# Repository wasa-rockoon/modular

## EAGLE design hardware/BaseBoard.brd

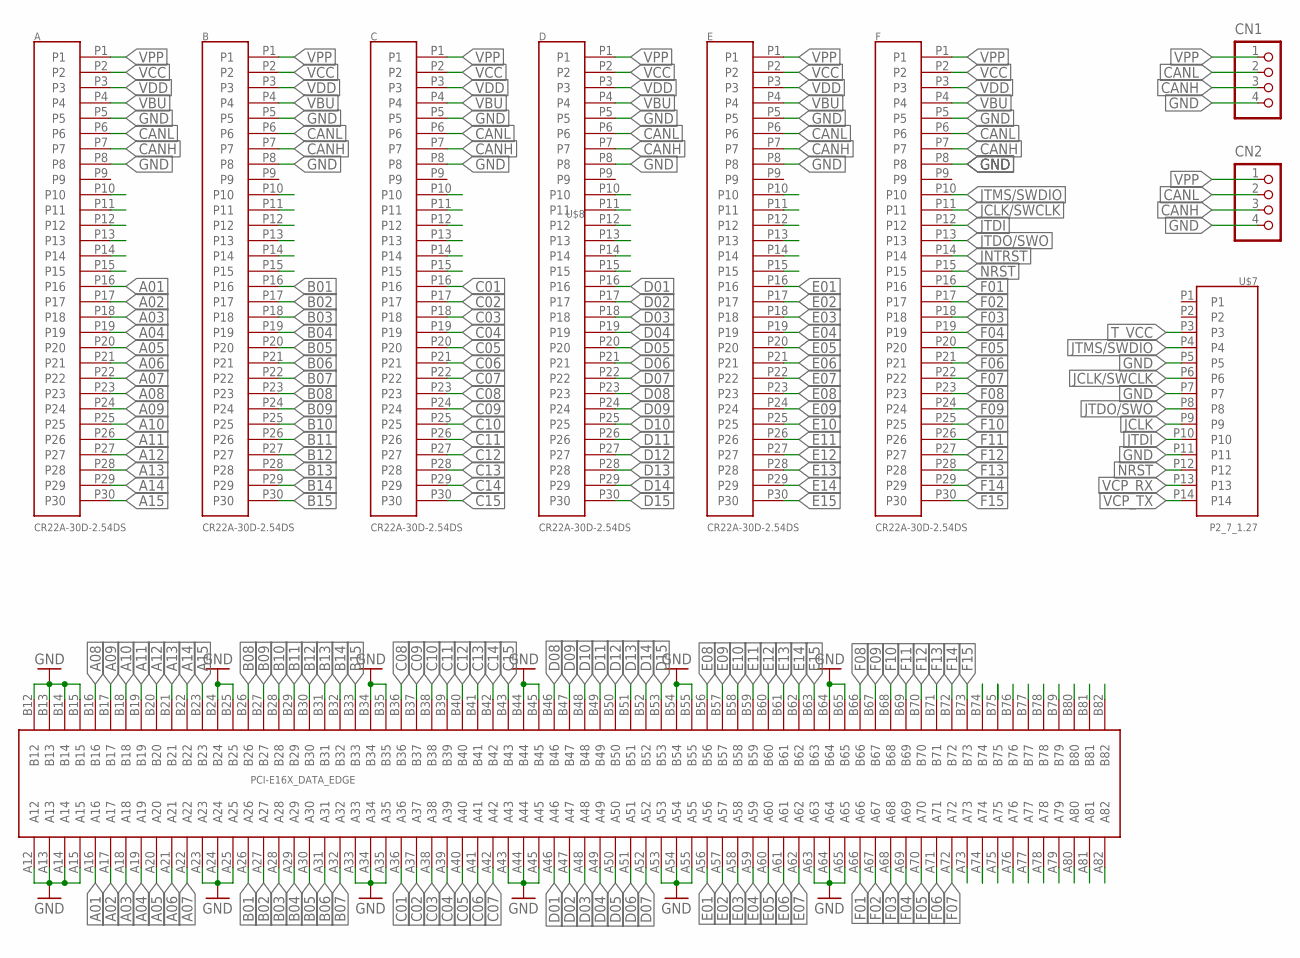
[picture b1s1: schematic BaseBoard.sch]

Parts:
A: CR22A-30D-2.54DS
B: CR22A-30D-2.54DS
C: CR22A-30D-2.54DS
CN1, CN2: B4B-PH-K-S
D: CR22A-30D-2.54DS
E: CR22A-30D-2.54DS
F: CR22A-30D-2.54DS
U$7: P2_7_1.27
U$8: PCI-E16X_DATA_EDGE; PCI-E_164_DATA_EDGE

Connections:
!JNTRST!: F.P14
!NRST!: F.P15, U$7.P12
A01: A.P16, U$8.A16
A02: A.P17, U$8.A17
A03: A.P18, U$8.A18
A04: A.P19, U$8.A19
A05: A.P20, U$8.A20
A06: A.P21, U$8.A21
A07: A.P22, U$8.A22
A08: A.P23, U$8.B16
A09: A.P24, U$8.B17
A10: A.P25, U$8.B18
A11: A.P26, U$8.B19
A12: A.P27, U$8.B20
A13: A.P28, U$8.B21
A14: A.P29, U$8.B22
A15: A.P30, U$8.B23
B01: B.P16, U$8.A26
B02: B.P17, U$8.A27
B03: B.P18, U$8.A28
B04: B.P19, U$8.A29
B05: B.P20, U$8.A30
B06: B.P21, U$8.A31
B07: B.P22, U$8.A32
B08: B.P23, U$8.B26
B09: B.P24, U$8.B27
B10: B.P25, U$8.B28
B11: B.P26, U$8.B29
B12: B.P27, U$8.B30
B13: B.P28, U$8.B31
B14: B.P29, U$8.B32
B15: B.P30, U$8.B33
C01: C.P16, U$8.A36
C02: C.P17, U$8.A37
C03: C.P18, U$8.A38
C04: C.P19, U$8.A39
C05: C.P20, U$8.A40
C06: C.P21, U$8.A41
C07: C.P22, U$8.A42
C08: C.P23, U$8.B36
C09: C.P24, U$8.B37
C10: C.P25, U$8.B38
C11: C.P26, U$8.B39
C12: C.P27, U$8.B40
C13: C.P28, U$8.B41
C14: C.P29, U$8.B42
C15: C.P30, U$8.B43
CANH: A.P7, B.P7, C.P7, CN1.3, CN2.3, D.P7, E.P7, F.P7
CANL: A.P6, B.P6, C.P6, CN1.2, CN2.2, D.P6, E.P6, F.P6
D01: D.P16, U$8.A46
D02: D.P17, U$8.A47
D03: D.P18, U$8.A48
D04: D.P19, U$8.A49
D05: D.P20, U$8.A50
D06: D.P21, U$8.A51
D07: D.P22, U$8.A52
D08: D.P23, U$8.B46
D09: D.P24, U$8.B47
D10: D.P25, U$8.B48
D11: D.P26, U$8.B49
D12: D.P27, U$8.B50
D13: D.P28, U$8.B51
D14: D.P29, U$8.B52
D15: D.P30, U$8.B53
E01: E.P16, U$8.A56
E02: E.P17, U$8.A57
E03: E.P18, U$8.A58
E04: E.P19, U$8.A59
E05: E.P20, U$8.A60
E06: E.P21, U$8.A61
E07: E.P22, U$8.A62
E08: E.P23, U$8.B56
E09: E.P24, U$8.B57
E10: E.P25, U$8.B58
E11: E.P26, U$8.B59
E12: E.P27, U$8.B60
E13: E.P28, U$8.B61
E14: E.P29, U$8.B62
E15: E.P30, U$8.B63
F01: F.P16, U$8.A66
F02: F.P17, U$8.A67
F03: F.P18, U$8.A68
F04: F.P19, U$8.A69
F05: F.P20, U$8.A70
F06: F.P21, U$8.A71
F07: F.P22, U$8.A72
F08: F.P23, U$8.B66
F09: F.P24, U$8.B67
F10: F.P25, U$8.B68
F11: F.P26, U$8.B69
F12: F.P27, U$8.B70
F13: F.P28, U$8.B71
F14: F.P29, U$8.B72
F15: F.P30, U$8.B73
GND: A.P5, A.P8, B.P5, B.P8, C.P5, C.P8, CN1.4, CN2.4, D.P5, D.P8, E.P5, E.P8, F.P5, F.P8, U$7.P5, U$7.P7, U$7.P11, U$8.A12, U$8.A13, U$8.A14, U$8.A15, U$8.A23, U$8.A24, U$8.A25, U$8.A33, U$8.A34, U$8.A35, U$8.A43, U$8.A44, U$8.A45, U$8.A53, U$8.A54, U$8.A55, U$8.A63, U$8.A64, U$8.A65, U$8.B12, U$8.B13, U$8.B14, U$8.B15, U$8.B24, U$8.B25, U$8.B34, U$8.B35, U$8.B44, U$8.B45, U$8.B54, U$8.B55, U$8.B64, U$8.B65
JCLK: U$7.P9
JCLK/SWCLK: F.P11, U$7.P6
JTDI: F.P12, U$7.P10
JTDO/SWO: F.P13, U$7.P8
JTMS/SWDIO: F.P10, U$7.P4
T_VCC: U$7.P3
VBU: A.P4, B.P4, C.P4, D.P4, E.P4, F.P4
VCC: A.P2, B.P2, C.P2, D.P2, E.P2, F.P2
VCP_RX: U$7.P13
VCP_TX: U$7.P14
VDD: A.P3, B.P3, C.P3, D.P3, E.P3, F.P3
VPP: A.P1, B.P1, C.P1, CN1.1, CN2.1, D.P1, E.P1, F.P1

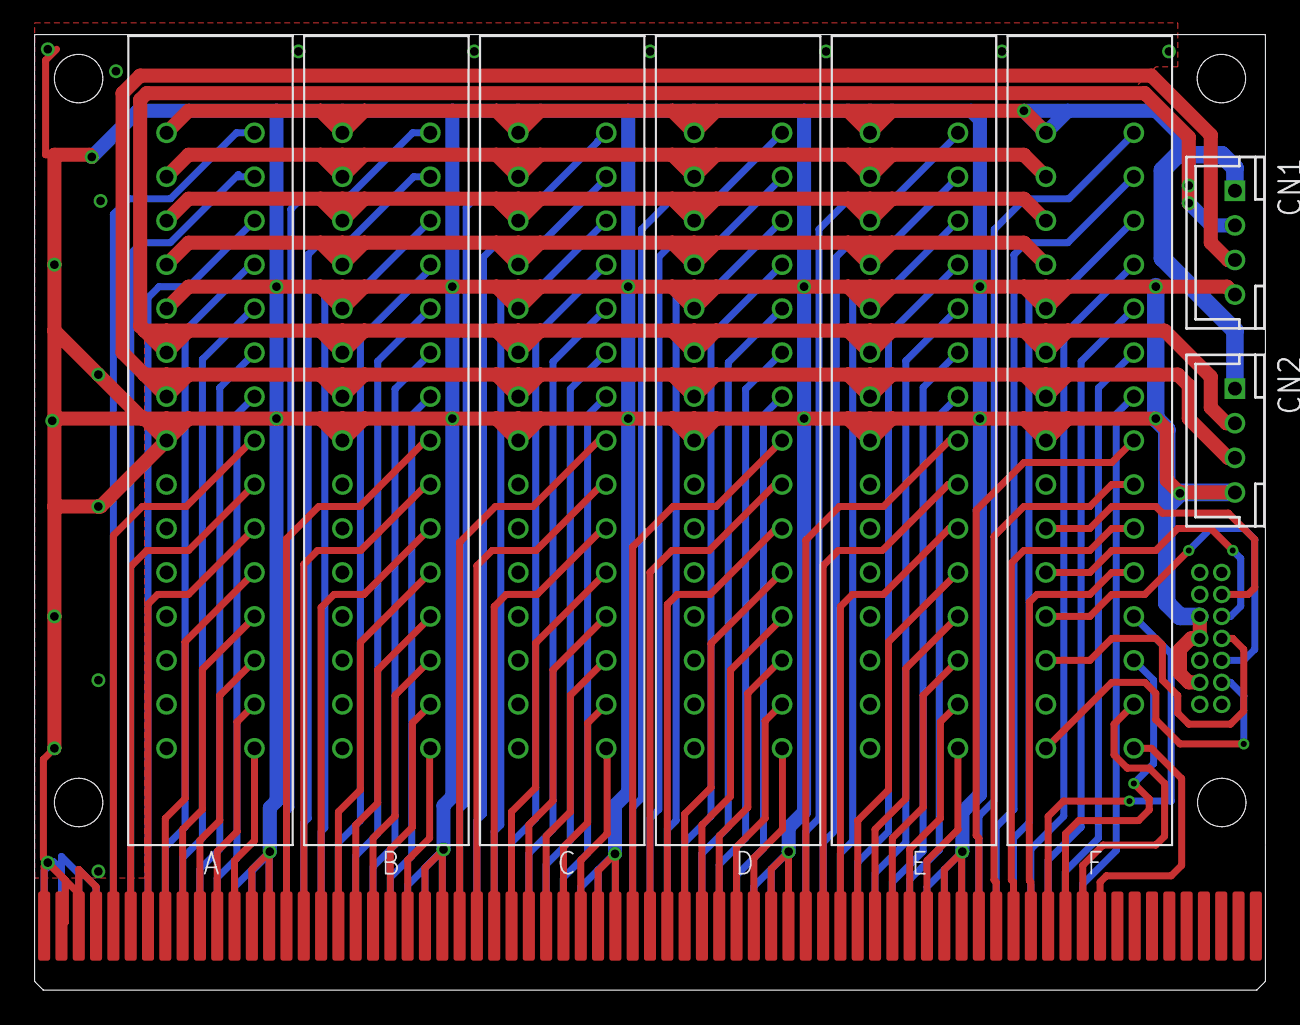
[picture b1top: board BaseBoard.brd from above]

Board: 2 copper layers, 71.1 x 55.2 mm, 10 parts (0 on the bottom side), 102 nets.

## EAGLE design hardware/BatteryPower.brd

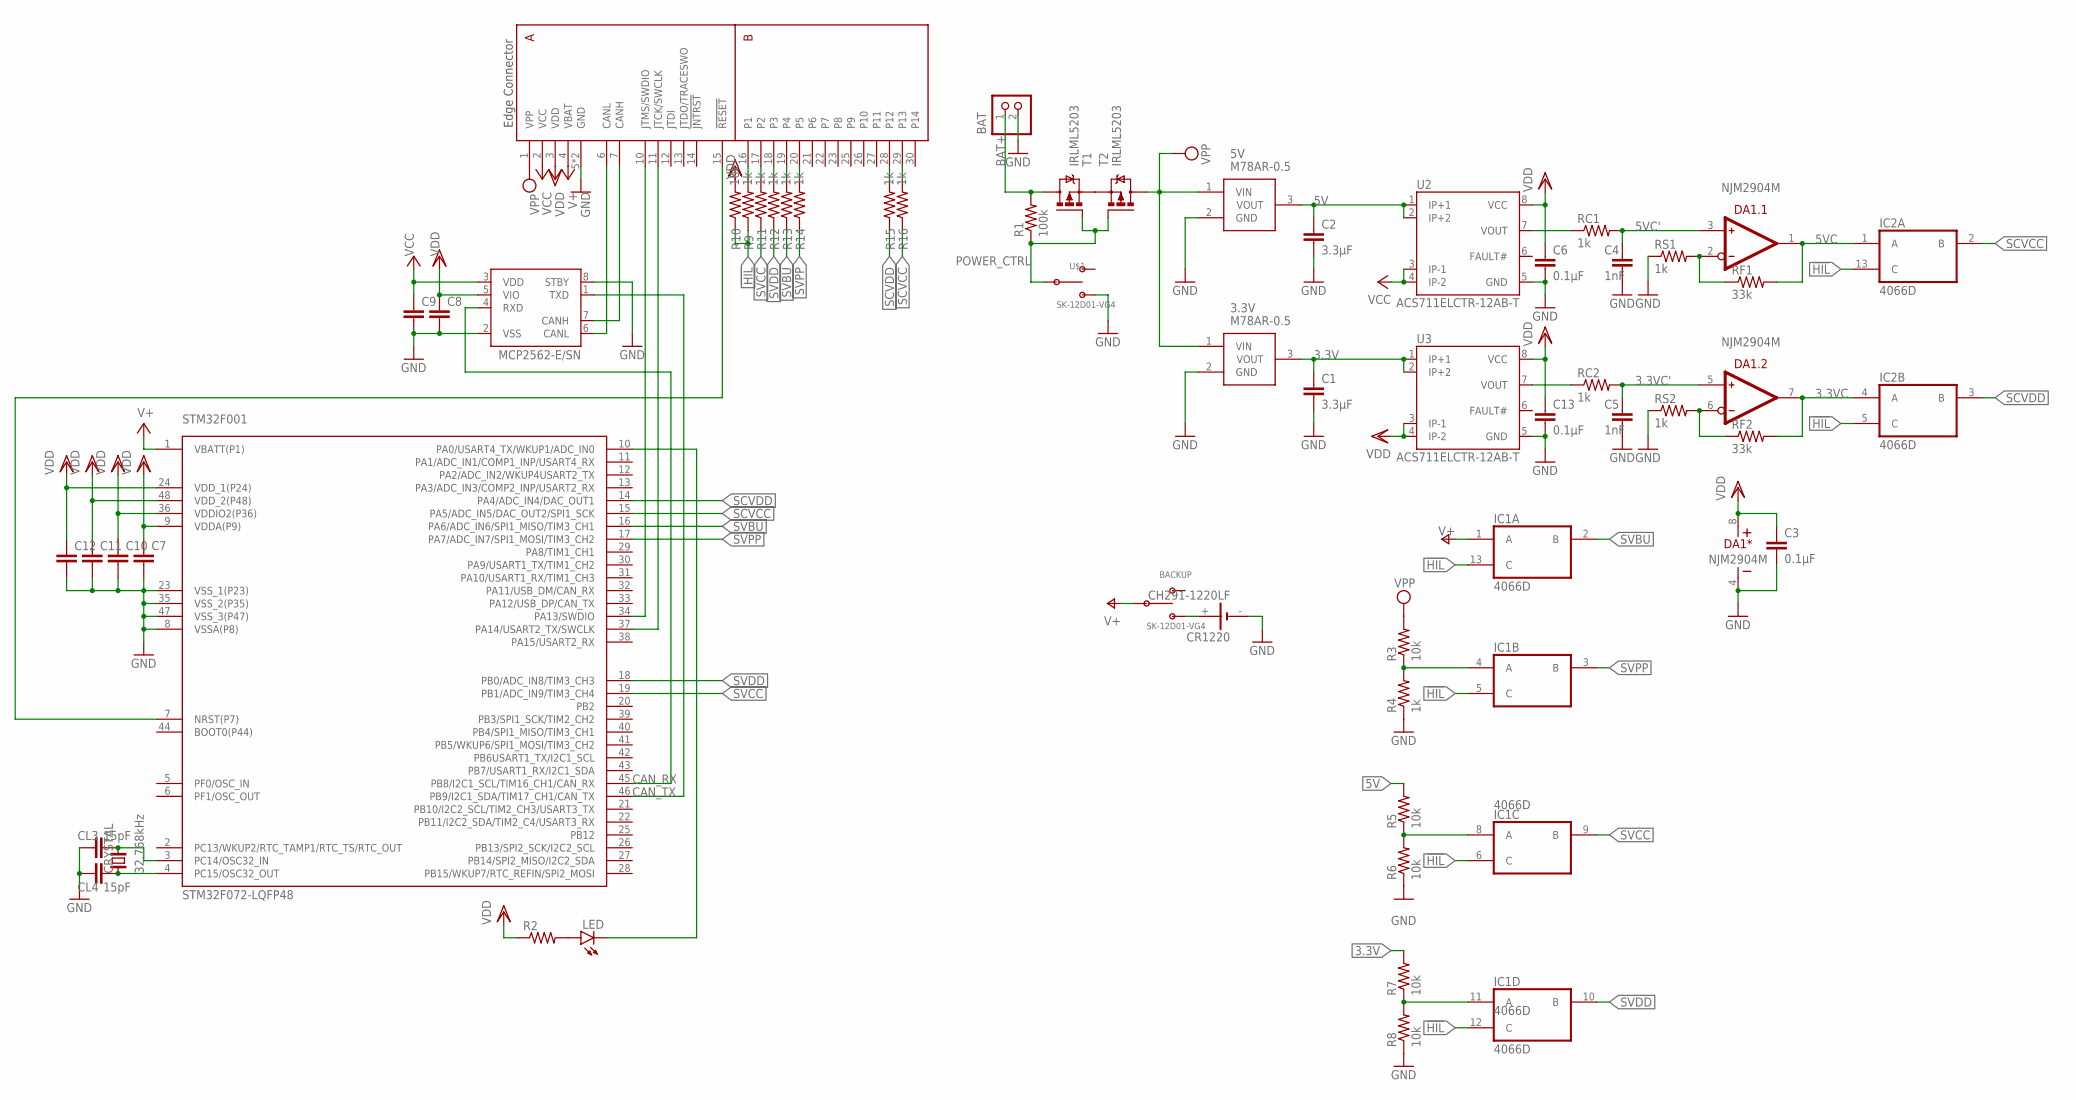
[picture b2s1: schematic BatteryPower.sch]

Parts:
3.3V, 5V: M78AR-0.5; SHDR3W75P0X254_1X3_1128X755X10
BACKUP: SK-12D01-VG4
BAT: S2B-XH-A
C1, C2: 3.3µF; C0603K
C3, C6, C13: 0.1µF; C0603K
C4, C5: 1nF; C0603K
C7, C8, C9, C10, C11, C12: C-EUC0603K; C0603K
CL3, CL4: 15pF; C0603K
CR1220: CH291-1220LF
CRYSTAL: 32.768kHz; FC-255
DA1: NJM2904M; SO-8
IC1, IC2: 4066D; SO14
LED: LEDCHIP-LED0603; CHIP-LED0603
MCP2562: MCP2562-E/SN; SOIC127P600X175-8N
R1: 100k; R0603
R2: R-US_R0603; R0603
R3, R5, R6, R7, R8, R10: 10k; R0603
R4, R9, R11, R12, R13, R14, R15, R16: 1k; R0603
RC1, RC2: 1k; R0603
RF1, RF2: 33k; R0603
RS1, RS2: 1k; R0603
STM32F001: STM32F072-LQFP48; LQFP48
T1, T2: IRLML5203; MICRO3
U2, U3: ACS711ELCTR-12AB-T; SOIC8
U$1: SK-12D01-VG4
U$2: EDGE30

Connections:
3.3V: 3.3V.3 (VOUT), C1.1, R7.2, U3.1 (IP+1), U3.2 (IP+2)
3.3VC: DA1.7 (OUT), IC2.4 (A), RF2.2
3.3VC': C5.1, DA1.5 (IN+), RC2.2
5V: 5V.3 (VOUT), C2.1, R5.2, U2.1 (IP+1), U2.2 (IP+2)
5VC: DA1.1 (OUT), IC2.1 (A), RF1.2
5VC': C4.1, DA1.3 (IN+), RC1.2
!HIL!: IC1.5 (C), IC1.6 (C), IC1.12 (C), IC1.13 (C), IC2.5 (C), IC2.13 (C), R9.1, R10.1
BAT+: BAT.1, R1.2, T1.3 (D)
BU+: BACKUP.B, CR1220.+
CANH1: MCP2562.7 (CANH), U$2.7 (CANH)
CANL1: MCP2562.6 (CANL), U$2.6 (CANL)
CAN_RX: MCP2562.4 (RXD), STM32F001.45 (PB8/I2C1_SCL/TIM16_CH1/CAN_RX)
CAN_TX: MCP2562.1 (TXD), STM32F001.46 (PB9/I2C1_SDA/TIM17_CH1/CAN_TX)
GND: 3.3V.2 (GND), 5V.2 (GND), BAT.2, C1.2, C2.2, C3.2, C4.2, C5.2, C6.2, C7.2, C8.2, C9.2, C10.2, C11.2, C12.2, C13.2, CL3.1, CL4.1, CR1220.-, DA1.4 (V-), IC1.7 (VSS), IC2.7 (VSS), MCP2562.2 (VSS), MCP2562.8 (STBY), R4.1, R6.1, R8.1, RS1.1, RS2.1, STM32F001.8 (VSSA(P8)), STM32F001.23 (VSS_1(P23)), STM32F001.35 (VSS_2(P35)), STM32F001.47 (VSS_3(P47)), U2.5 (GND), U3.5 (GND), U$1.B, U$2.5 (GND), U$2.8 (GND)
unnamed: R9.2, U$2.16 (P1)
unnamed: T1.2 (S), T2.2 (S)
unnamed: DA1.2 (IN-), RF1.1, RS1.2
unnamed: DA1.6 (IN-), RF2.1, RS2.2
unnamed: RC1.1, U2.7 (VOUT)
unnamed: RC2.1, U3.7 (VOUT)
unnamed: R16.2, U$2.29 (P13)
unnamed: R15.2, U$2.28 (P12)
unnamed: R14.2, U$2.20 (P5)
unnamed: R13.2, U$2.19 (P4)
unnamed: R12.2, U$2.18 (P3)
unnamed: CL4.2, CRYSTAL.1, STM32F001.4 (PC15/OSC32_OUT)
unnamed: CL3.2, CRYSTAL.2, STM32F001.3 (PC14/OSC32_IN)
unnamed: LED.C, STM32F001.10 (PA0/USART4_TX/WKUP1/ADC_IN0)
unnamed: R11.2, U$2.17 (P2)
unnamed: LED.A, R2.2
NRST1: STM32F001.7 (NRST(P7)), U$2.15 (!RESET!)
POWER_CTRL: R1.1, T1.1 (G), T2.1 (G), U$1.C
PVCC: IC1.8 (A), R5.1, R6.2
PVDD: IC1.11 (A), R7.1, R8.2
PVPP: IC1.4 (A), R3.1, R4.2
SCVCC: IC2.2 (B), R16.1, STM32F001.15 (PA5/ADC_IN5/DAC_OUT2/SPI1_SCK)
SCVDD: IC2.3 (B), R15.1, STM32F001.14 (PA4/ADC_IN4/DAC_OUT1)
SVBU: IC1.2 (B), R13.1, STM32F001.16 (PA6/ADC_IN6/SPI1_MISO/TIM3_CH1)
SVCC: IC1.9 (B), R11.1, STM32F001.19 (PB1/ADC_IN9/TIM3_CH4)
SVDD: IC1.10 (B), R12.1, STM32F001.18 (PB0/ADC_IN8/TIM3_CH3)
SVPP: IC1.3 (B), R14.1, STM32F001.17 (PA7/ADC_IN7/SPI1_MOSI/TIM3_CH2)
SWCLK1: STM32F001.37 (PA14/USART2_TX/SWCLK), U$2.11 (JTCK/SWCLK)
SWDIO1: STM32F001.34 (PA13/SWDIO), U$2.10 (JTMS/SWDIO)
VBAT: BACKUP.C, IC1.1 (A), STM32F001.1 (VBATT(P1)), U$2.4 (VBAT)
VCC: C9.1, MCP2562.3 (VDD), U2.3 (IP-1), U2.4 (IP-2), U$2.2 (VCC)
VDD: C3.1, C6.1, C7.1, C8.1, C10.1, C11.1, C12.1, C13.1, DA1.8 (V+), IC1.14 (VDD), IC2.14 (VDD), MCP2562.5 (VIO), R2.1, R10.2, STM32F001.9 (VDDA(P9)), STM32F001.24 (VDD_1(P24)), STM32F001.36 (VDDIO2(P36)), STM32F001.48 (VDD_2(P48)), U2.8 (VCC), U3.3 (IP-1), U3.4 (IP-2), U3.8 (VCC), U$2.3 (VDD)
VPP: 3.3V.1 (VIN), 5V.1 (VIN), R3.2, T2.3 (D), U$2.1 (VPP)

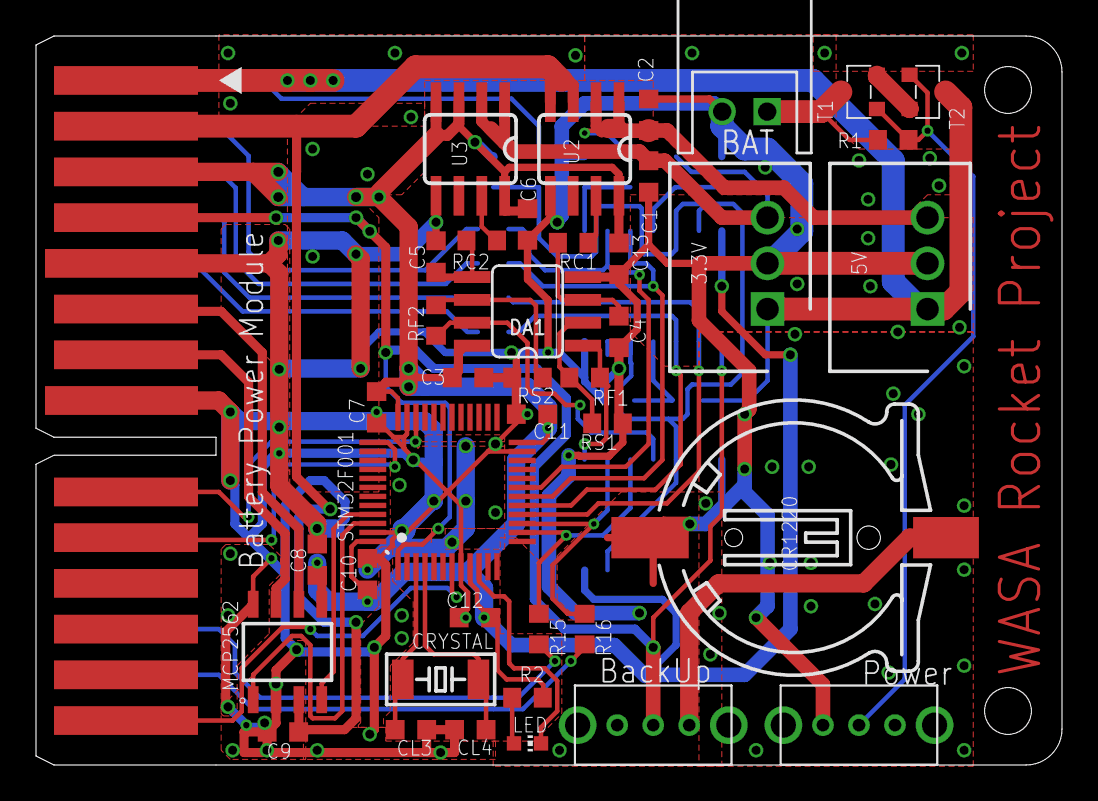
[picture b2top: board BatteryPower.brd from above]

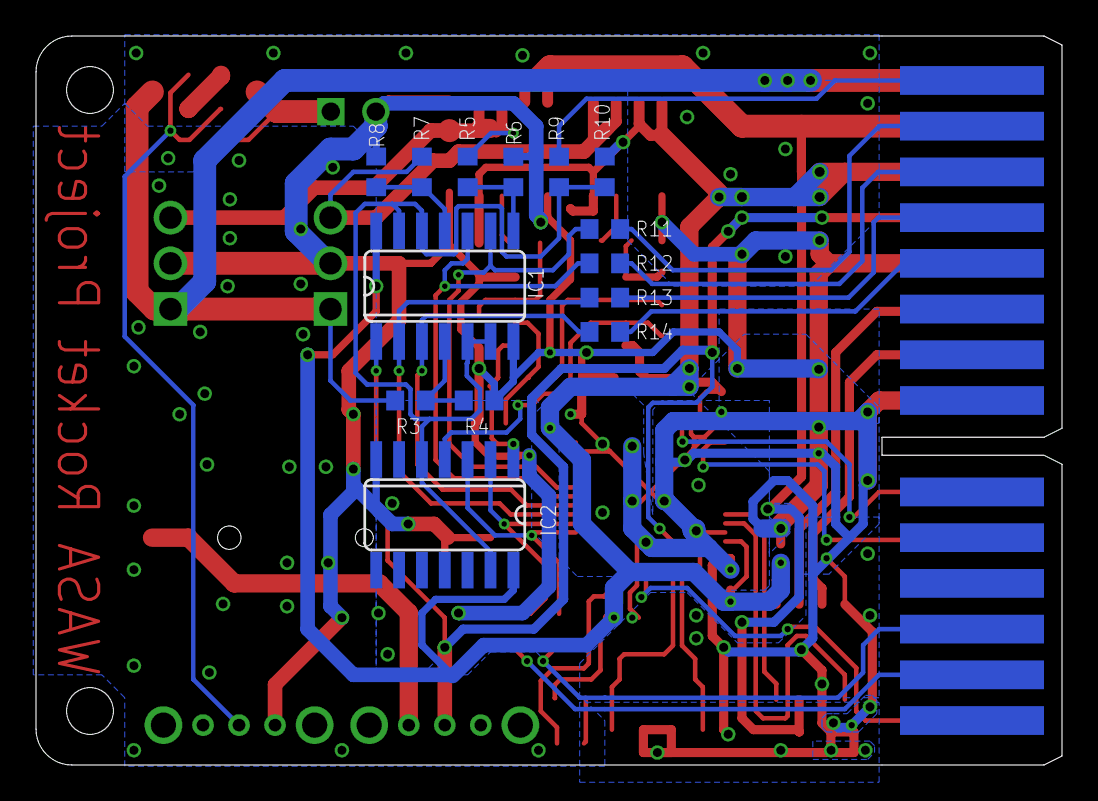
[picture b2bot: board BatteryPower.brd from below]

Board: 2 copper layers, 57.0 x 40.5 mm, 55 parts (14 on the bottom side), 47 nets.

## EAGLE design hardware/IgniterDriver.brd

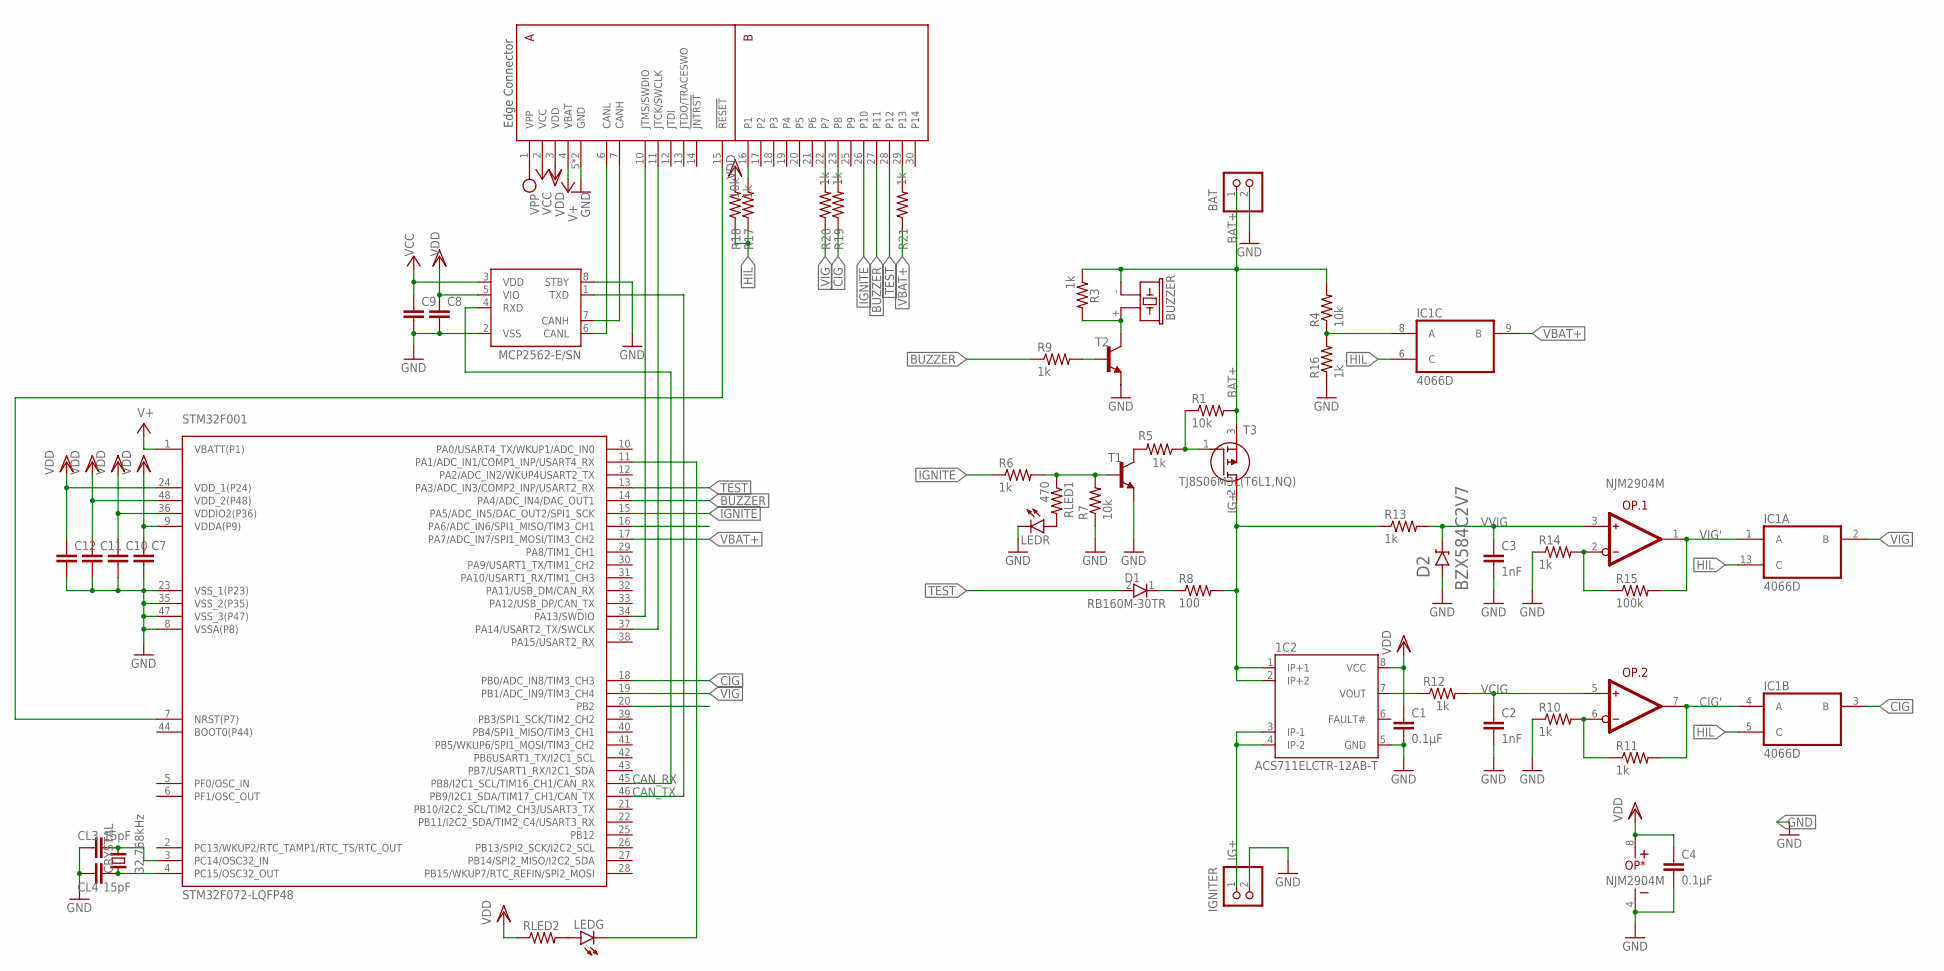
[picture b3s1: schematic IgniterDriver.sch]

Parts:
1C2: ACS711ELCTR-12AB-T; SOIC8
BAT: S2B-XH-A
BUZZER: F/CM12P
C1, C4: 0.1µF; C0603K
C2, C3: 1nF; C0603K
C7, C8, C9, C10, C11, C12: C-EUC0603K; C0603K
CL3, CL4: 15pF; C0603K
CRYSTAL: 32.768kHz; FC-255
D1: RB160M-30TR; SODFL3516X90N
D2: BZX584C2V7; BZX584C
IC1: 4066D; SO14
IGNITER: S2B-XH-A
LEDG: LEDCHIP-LED0603; CHIP-LED0603
LEDR: LEDCHIPLED_0603; CHIPLED_0603
MCP2562: MCP2562-E/SN; SOIC127P600X175-8N
OP: NJM2904M; SO-8
R1, R4, R7, R18: 10k; R0603
R3, R5, R6, R9, R10, R11, R12, R13, R14, R16, R17, R19, R20, R21: 1k; R0603
R8: 100; R0603
R15: 100k; R0603
RLED1: 470; R0603
RLED2: R-US_R0603; R0603
STM32F001: STM32F072-LQFP48; LQFP48
T1, T2: -NPN-SOT23-EBC; SOT23-EBC
T3: TJ8S06M3L(T6L1,NQ); TJ8S06M3LT6L1NQ
U$2: EDGE30

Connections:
!HIL!: IC1.5 (C), IC1.6 (C), IC1.13 (C), R17.1, R18.1
BAT+: BAT.1, BUZZER.- (2), R1.2, R3.1, R4.2, T3.3 (S)
BUZZER: R9.1, STM32F001.14 (PA4/ADC_IN4/DAC_OUT1), U$2.27 (P11)
CANH1: MCP2562.7 (CANH), U$2.7 (CANH)
CANL1: MCP2562.6 (CANL), U$2.6 (CANL)
CAN_RX: MCP2562.4 (RXD), STM32F001.45 (PB8/I2C1_SCL/TIM16_CH1/CAN_RX)
CAN_TX: MCP2562.1 (TXD), STM32F001.46 (PB9/I2C1_SDA/TIM17_CH1/CAN_TX)
CIG: IC1.3 (B), R19.1, STM32F001.18 (PB0/ADC_IN8/TIM3_CH3)
CIG': IC1.4 (A), OP.7 (OUT), R11.2
GND: 1C2.5 (GND), BAT.2, C1.2, C2.2, C3.2, C4.2, C7.2, C8.2, C9.2, C10.2, C11.2, C12.2, CL3.1, CL4.1, D2.A, IC1.7 (VSS), IGNITER.2, LEDR.C, MCP2562.2 (VSS), MCP2562.8 (STBY), OP.4 (V-), R7.1, R10.1, R14.1, R16.1, STM32F001.8 (VSSA(P8)), STM32F001.23 (VSS_1(P23)), STM32F001.35 (VSS_2(P35)), STM32F001.47 (VSS_3(P47)), T1.E, T2.E, U$2.5 (GND), U$2.8 (GND)
IG+: 1C2.3 (IP-1), 1C2.4 (IP-2), IGNITER.1
IG+': 1C2.1 (IP+1), 1C2.2 (IP+2), R8.2, R13.1, T3.2 (D)
IGNITE: R6.1, STM32F001.15 (PA5/ADC_IN5/DAC_OUT2/SPI1_SCK), U$2.26 (P10)
unnamed: R1.1, R5.1, T3.1 (G)
unnamed: R5.2, T1.C
unnamed: R6.2, R7.2, RLED1.1, T1.B
unnamed: D1.1 (K), R8.1
unnamed: BUZZER.+ (1), R3.2, T2.C
unnamed: OP.2 (IN-), R14.2, R15.1
unnamed: OP.6 (IN-), R10.2, R11.1
unnamed: LEDR.A, RLED1.2
unnamed: R9.2, T2.B
unnamed: R21.2, U$2.29 (P13)
unnamed: R19.2, U$2.23 (P8)
unnamed: R20.2, U$2.22 (P7)
unnamed: CL4.2, CRYSTAL.1, STM32F001.4 (PC15/OSC32_OUT)
unnamed: CL3.2, CRYSTAL.2, STM32F001.3 (PC14/OSC32_IN)
unnamed: LEDG.C, STM32F001.11 (PA1/ADC_IN1/COMP1_INP/USART4_RX)
unnamed: R17.2, U$2.16 (P1)
unnamed: LEDG.A, RLED2.2
NRST1: STM32F001.7 (NRST(P7)), U$2.15 (!RESET!)
SWCLK1: STM32F001.37 (PA14/USART2_TX/SWCLK), U$2.11 (JTCK/SWCLK)
SWDIO1: STM32F001.34 (PA13/SWDIO), U$2.10 (JTMS/SWDIO)
TEST: D1.2 (A), STM32F001.13 (PA3/ADC_IN3/COMP2_INP/USART2_RX), U$2.28 (P12)
VBAT+: IC1.9 (B), R21.1, STM32F001.17 (PA7/ADC_IN7/SPI1_MOSI/TIM3_CH2)
VBAT+': IC1.8 (A), R4.1, R16.2
VBU: STM32F001.1 (VBATT(P1)), U$2.4 (VBAT)
VCC: C9.1, MCP2562.3 (VDD), U$2.2 (VCC)
VCIG: C2.1, OP.5 (IN+), R12.2
VDD: 1C2.8 (VCC), C1.1, C4.1, C7.1, C8.1, C10.1, C11.1, C12.1, IC1.14 (VDD), MCP2562.5 (VIO), OP.8 (V+), R18.2, RLED2.1, STM32F001.9 (VDDA(P9)), STM32F001.24 (VDD_1(P24)), STM32F001.36 (VDDIO2(P36)), STM32F001.48 (VDD_2(P48)), U$2.3 (VDD)
VIG: IC1.2 (B), R20.1, STM32F001.19 (PB1/ADC_IN9/TIM3_CH4)
VIG': IC1.1 (A), OP.1 (OUT), R15.2
VOUT: 1C2.7 (VOUT), R12.1
VPP: U$2.1 (VPP)
VVIG: C3.1, D2.C, OP.3 (IN+), R13.2

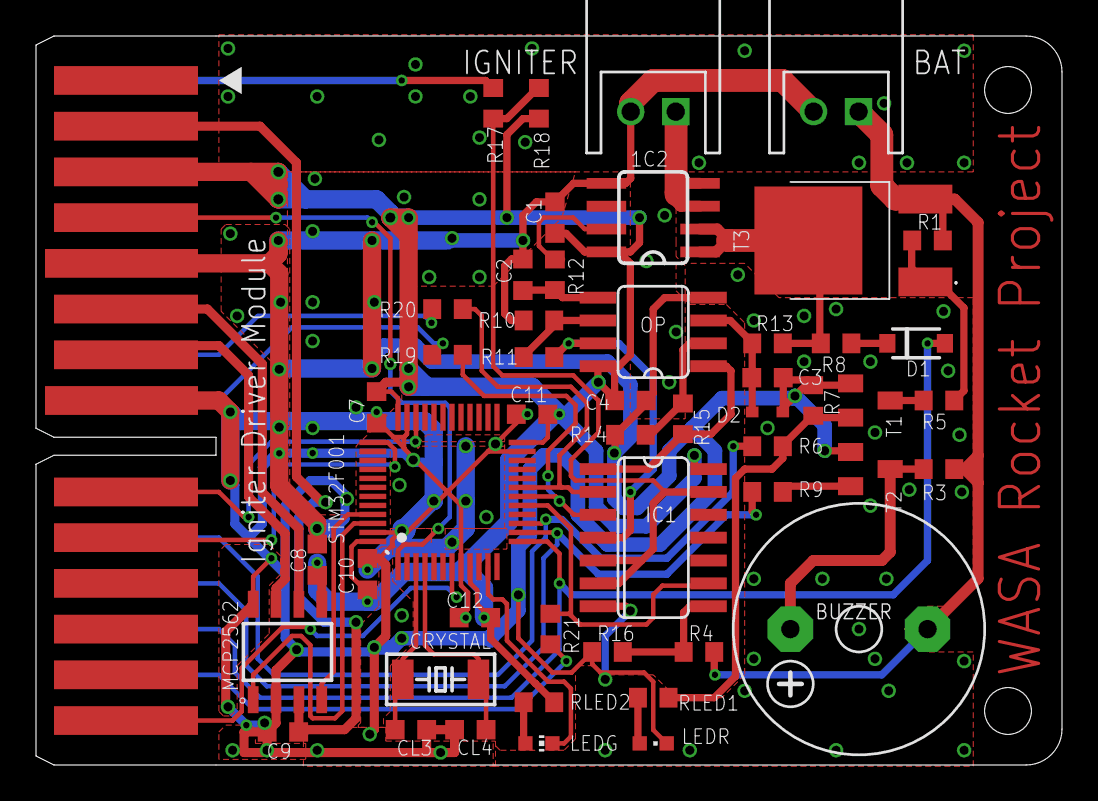
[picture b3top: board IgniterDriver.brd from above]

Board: 2 copper layers, 57.0 x 40.5 mm, 51 parts (0 on the bottom side), 44 nets.
